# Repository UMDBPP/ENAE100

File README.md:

# ENAE100
This repository is for the starter shields used in the ENAE100 Freshman Workshops during the fall semester

# Dependencies
* [OneWire](https://github.com/PaulStoffregen/OneWire) by Paul Stoffregen
* [DallasTemperature](https://github.com/milesburton/Arduino-Temperature-Control-Library) by Miles Burton
* [RTClib](https://github.com/adafruit/RTClib) by Adafruit

# Contents
## /Board
Gerbers and board files

## /Code/StarterShield
Working sample code for the board

# Notes/FAQ
1. SD Chip Select is Pin 10
2. LED is on pin 9

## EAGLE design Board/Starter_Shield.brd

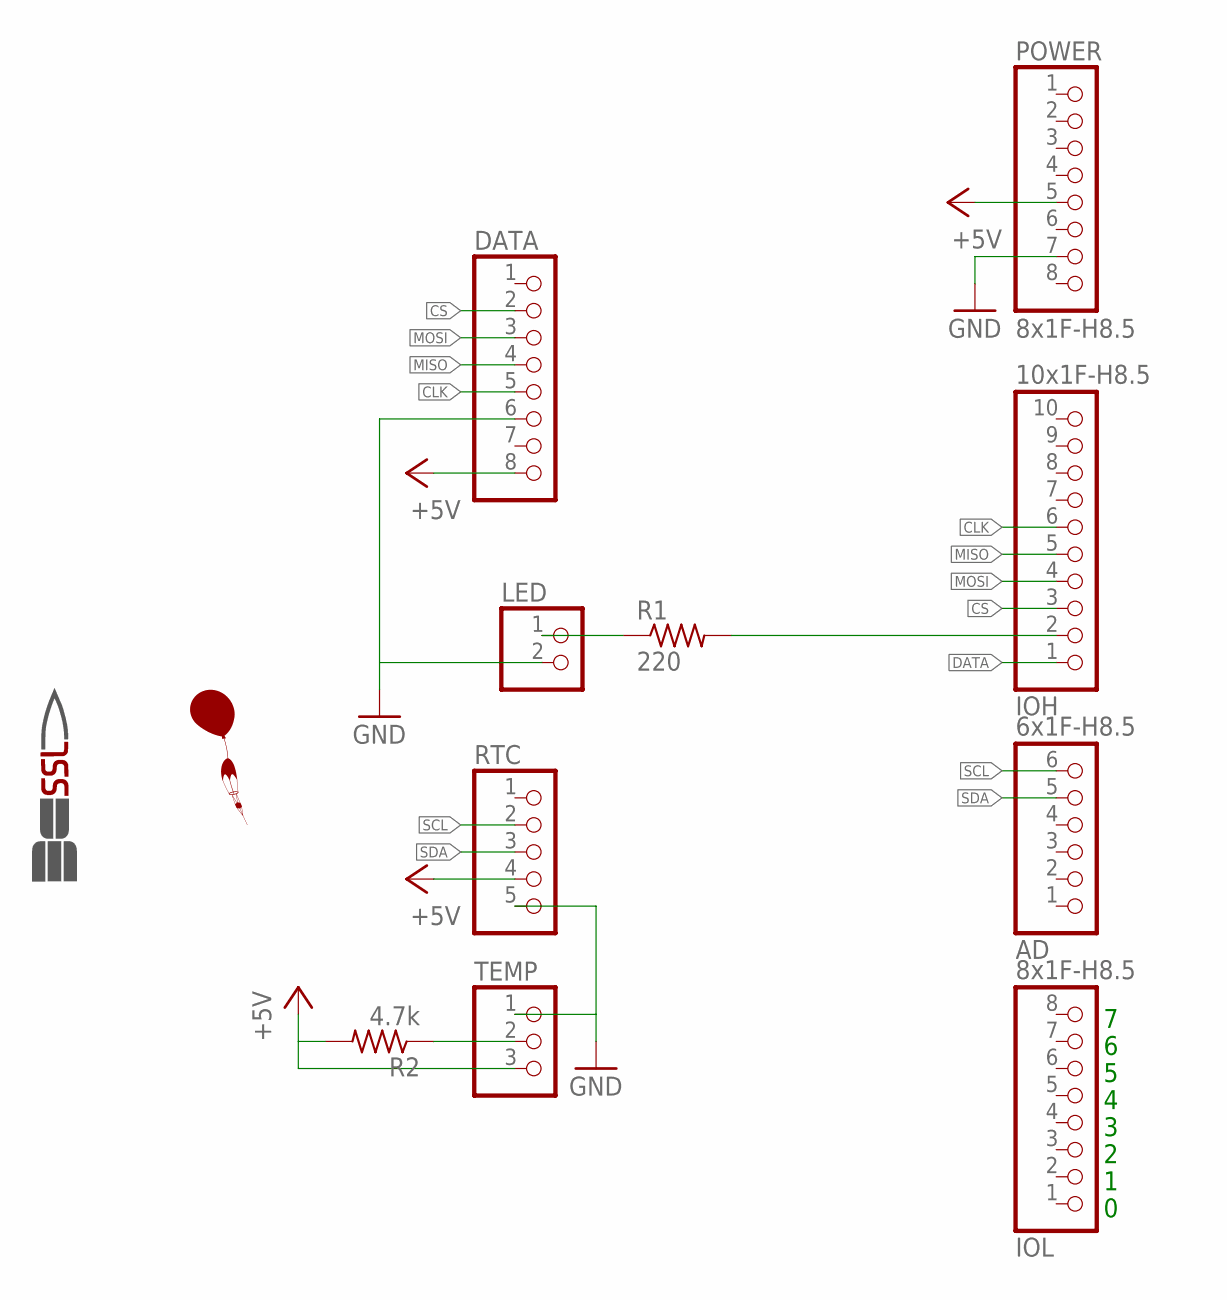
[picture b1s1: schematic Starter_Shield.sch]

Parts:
AD: 6x1F-H8.5; 1X06
DATA: PINHD-1X8; 1X08
IMAG1: SSL.53IN; SSL_.53IN
IOH: 10x1F-H8.5; 1X10
IOL: 8x1F-H8.5; 1X08
LED: PINHD-1X2; 1X02
POWER: 8x1F-H8.5; 1X08
R1: 220; 0207/10
R2: 4.7k; 0207/10
RTC: PINHD-1X5; 1X05
TEMP: PINHD-1X3; 1X03
U$1: BALLOON

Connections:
+5V: DATA.8, POWER.5, R2.2, RTC.4, TEMP.3
CLK: DATA.5, IOH.6
CS: DATA.2, IOH.3
DATA: IOH.1, R2.1, TEMP.2
GND: DATA.6, LED.2, POWER.7, RTC.5, TEMP.1
MISO: DATA.4, IOH.5
MOSI: DATA.3, IOH.4
unnamed: LED.1, R1.1
unnamed: IOH.2, R1.2
SCL: AD.6, RTC.2
SDA: AD.5, RTC.3

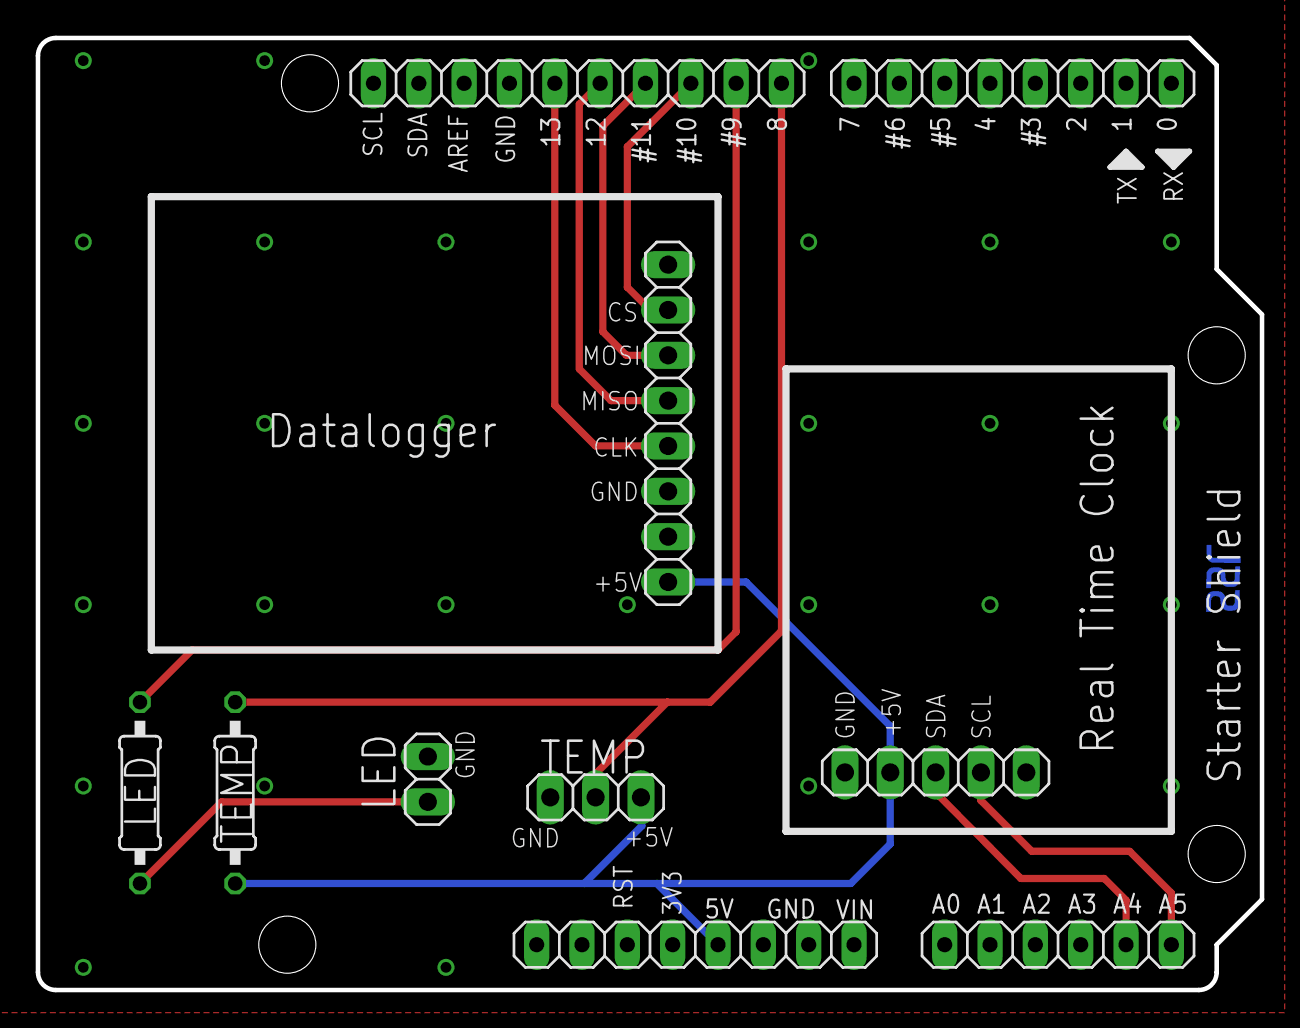
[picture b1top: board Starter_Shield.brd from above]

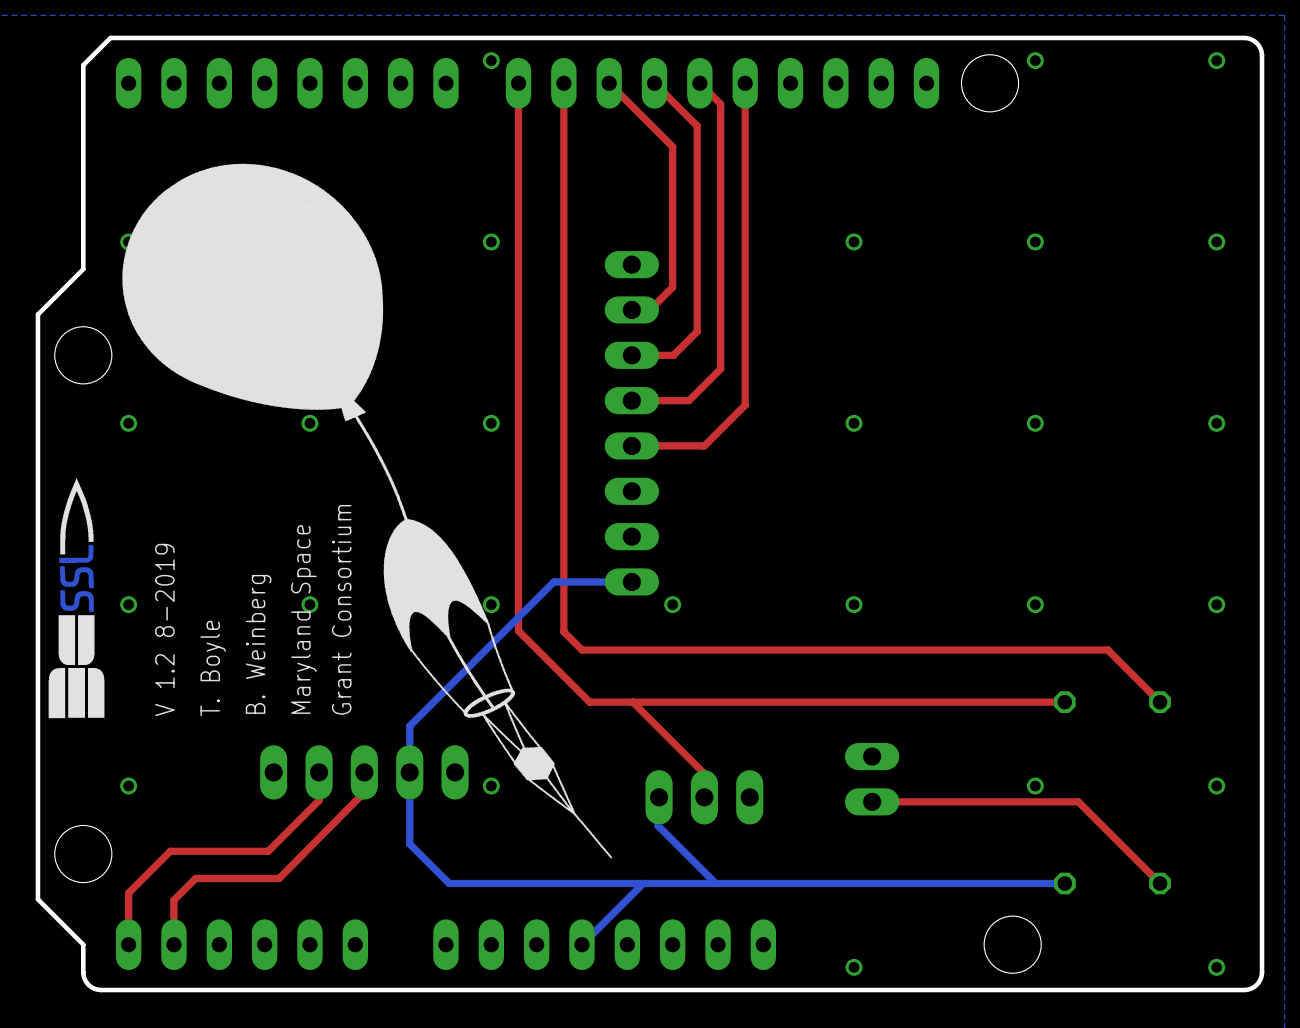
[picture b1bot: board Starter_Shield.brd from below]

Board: 2 copper layers, 68.6 x 53.3 mm, 12 parts (2 on the bottom side), 11 nets.

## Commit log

2019-01-03 readme and board files
2019-01-03 code
2019-08-28 updated gnd on the datalogger to the right pin - V1.2 now
2021-09-27 included comment in startershield.ino to specify which RTClib should be used
2021-09-28 took out rtc code so freshmen can do it themselves and learn!
2021-10-05 Made some changes
    added more comments
    changed output text formatting
    misc. style changes
2021-10-05 added dependencies to readme
2021-10-05 added a suggestion for freshman to create a print_time() function if they are feeling ambitious
2021-10-12 turned some strings into F() strings for efficiencey
2021-10-12 fixed bug, changed single quotes to double quotes
2022-02-15 added comment explaining RTC set-up process
